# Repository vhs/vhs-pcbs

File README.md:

vhs-pcbs
========

PCB designs from vhs events

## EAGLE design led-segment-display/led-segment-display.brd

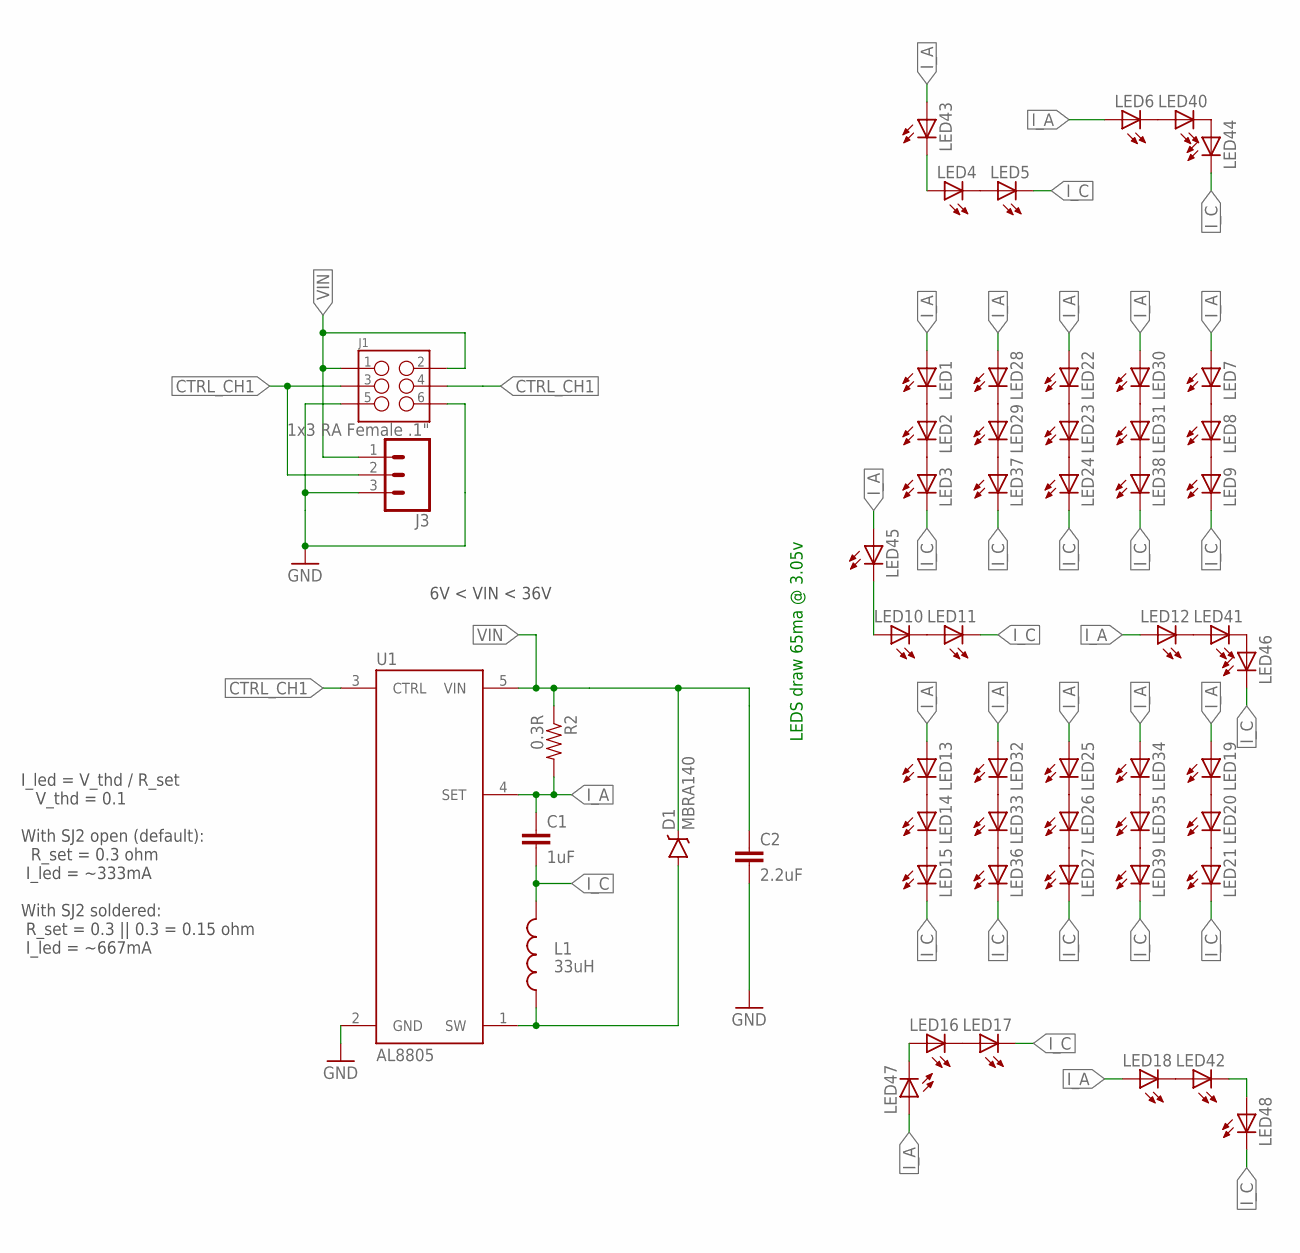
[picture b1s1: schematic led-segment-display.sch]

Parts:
C1: 1uF; 1206-CAP
C2: 2.2uF; 1206-CAP
D1: MBRA140; SMA-DIODE
J1: M03X2SMD; 2X3_SMD_2.54MM
J3: 1x3 RA Female .1"; 1X3_SMD_2.54MM
L1: 33uH; SRN6045
LED1, LED2, LED3, LED4, LED5, LED6, LED7, LED8, LED9, LED10, LED11, LED12, LED13, LED14, LED15, LED16, LED17, LED18, LED19, LED20, LED21, LED22, LED23, LED24, LED25, LED26, LED27, LED28, LED29, LED30, LED31, LED32, LED33, LED34, LED35, LED36, LED37, LED38, LED39, LED40, LED41, LED42, LED43, LED44, LED45, LED46, LED47, LED48: LED3014; LED-3014
R2: 0.3R; 0805
U1: AL8805; SOT23-5

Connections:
CTRL_CH1: J1.3, J1.4, J3.2, U1.3 (CTRL)
GND: C2.2, J1.5, J1.6, J3.3, U1.2 (GND)
I_A: C1.1, LED1.A, LED6.A, LED7.A, LED12.A, LED13.A, LED18.A, LED19.A, LED22.A, LED25.A, LED28.A, LED30.A, LED32.A, LED34.A, LED43.A, LED45.A, LED47.A, R2.2, U1.4 (SET)
I_C: C1.2, L1.2, LED3.C, LED5.C, LED9.C, LED11.C, LED15.C, LED17.C, LED21.C, LED24.C, LED27.C, LED36.C, LED37.C, LED38.C, LED39.C, LED44.C, LED46.C, LED48.C
unnamed: LED1.C, LED2.A
unnamed: LED2.C, LED3.A
unnamed: LED4.C, LED5.A
unnamed: LED4.A, LED43.C
unnamed: LED7.C, LED8.A
unnamed: LED8.C, LED9.A
unnamed: LED10.C, LED11.A
unnamed: LED40.C, LED44.A
unnamed: LED13.C, LED14.A
unnamed: LED14.C, LED15.A
unnamed: LED16.C, LED17.A
unnamed: LED42.C, LED48.A
unnamed: LED19.C, LED20.A
unnamed: LED20.C, LED21.A
unnamed: LED22.C, LED23.A
unnamed: LED23.C, LED24.A
unnamed: LED25.C, LED26.A
unnamed: LED26.C, LED27.A
unnamed: LED28.C, LED29.A
unnamed: LED30.C, LED31.A
unnamed: LED32.C, LED33.A
unnamed: LED34.C, LED35.A
unnamed: LED33.C, LED36.A
unnamed: LED29.C, LED37.A
unnamed: LED31.C, LED38.A
unnamed: LED35.C, LED39.A
unnamed: LED6.C, LED40.A
unnamed: LED12.C, LED41.A
unnamed: LED18.C, LED42.A
unnamed: LED16.A, LED47.C
unnamed: LED10.A, LED45.C
unnamed: LED41.C, LED46.A
SW: D1.A, L1.1, U1.1 (SW)
VIN: C2.1, D1.C, J1.1, J1.2, J3.1, R2.1, U1.5 (VIN)

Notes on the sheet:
LEDS draw 65ma @ 3.05v
I_led = V_thd / R_set V_thd = 0.1 With SJ2 open (default): R_set = 0.3 ohm I_led = ~333mA With SJ2 soldered: R_set = 0.3 || 0.3 = 0.15 ohm I_led = ~667mA
6V < VIN < 36V

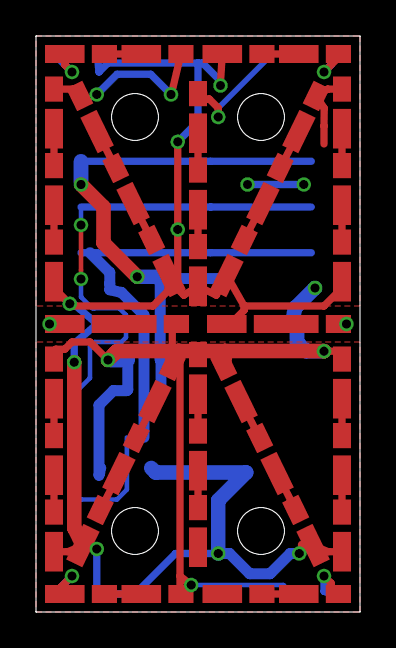
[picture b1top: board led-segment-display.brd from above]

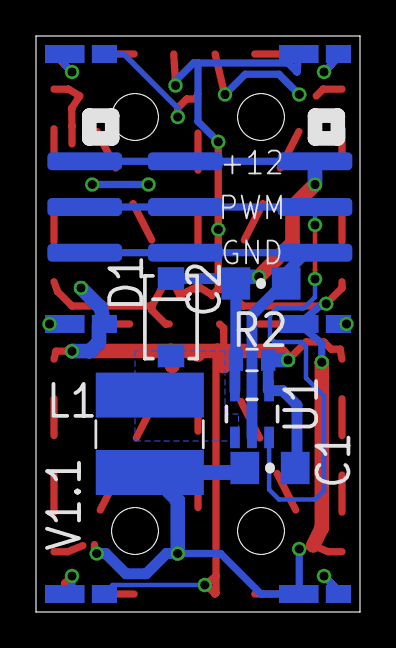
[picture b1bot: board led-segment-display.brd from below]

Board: 2 copper layers, 18.0 x 32.0 mm, 56 parts (14 on the bottom side), 38 nets.

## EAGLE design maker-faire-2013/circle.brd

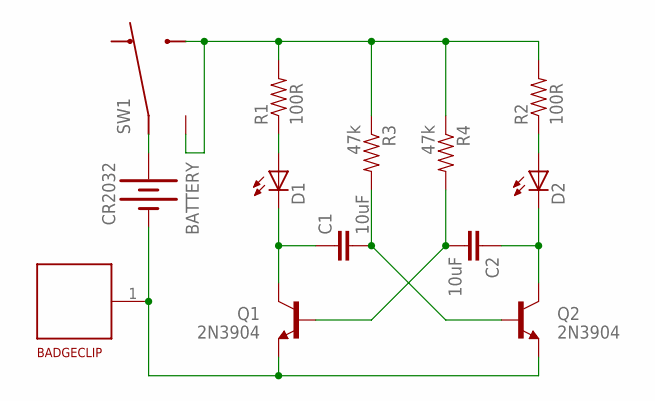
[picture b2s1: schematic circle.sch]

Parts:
BADGECLIP: BADGE_CLIP
BATTERY: CR2032; BATTCOM_20MM_PTH
C1, C2: 10uF; C050-024X044
D1, D2: LED5MM-KIT
Q1, Q2: 2N3904; TO-92-AMMO
R1, R2: 100R; AXIAL-0.4
R3, R4: 47k; AXIAL-0.4
SW1: 0S102011MS2QN1

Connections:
1: SW1.1
CASE2: R1.P$2 (2), R2.P$2 (2), R3.P$1 (1), R4.P$1 (1), SW1.3, SW1.CASE1 (CASE2), SW1.CASE2
GND: BADGECLIP.1, BATTERY.2 (-), Q1.1 (E), Q2.1 (E)
unnamed: BATTERY.1 (+), SW1.2
unnamed: C2.1, D2.K (C), Q2.3 (C)
unnamed: C1.1, D1.K (C), Q1.3 (C)
unnamed: C2.2, Q1.2 (B), R4.P$2 (2)
unnamed: C1.2, Q2.2 (B), R3.P$2 (2)
unnamed: D2.A, R2.P$1 (1)
unnamed: D1.A, R1.P$1 (1)

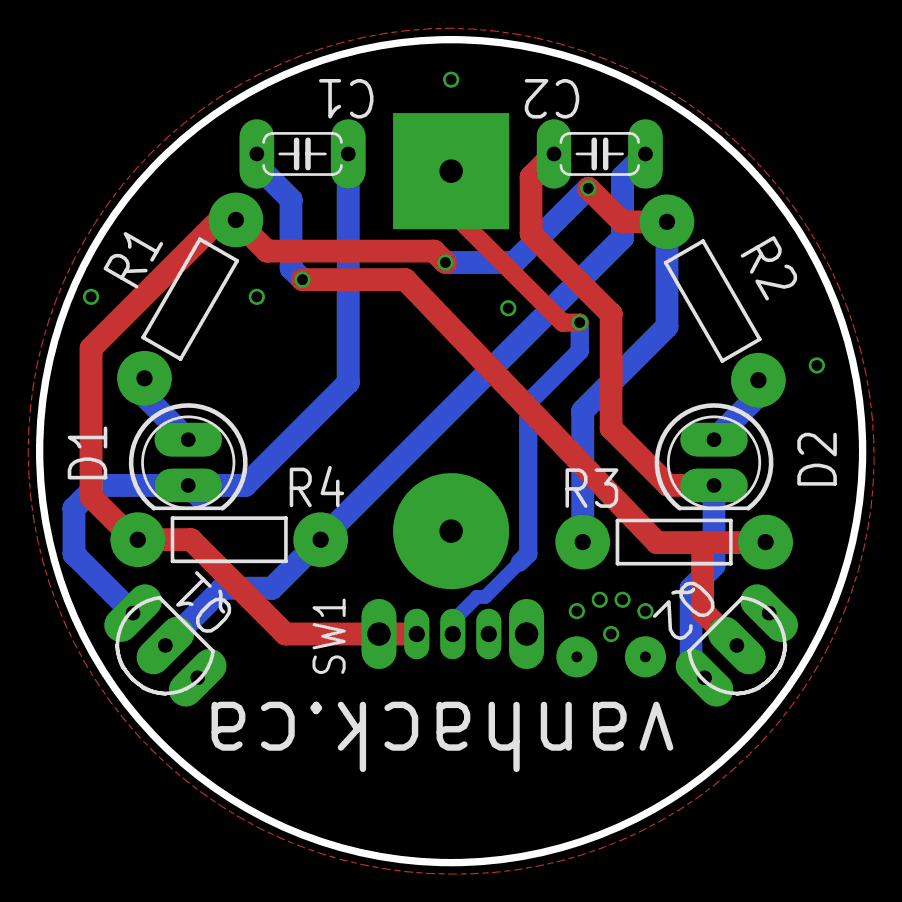
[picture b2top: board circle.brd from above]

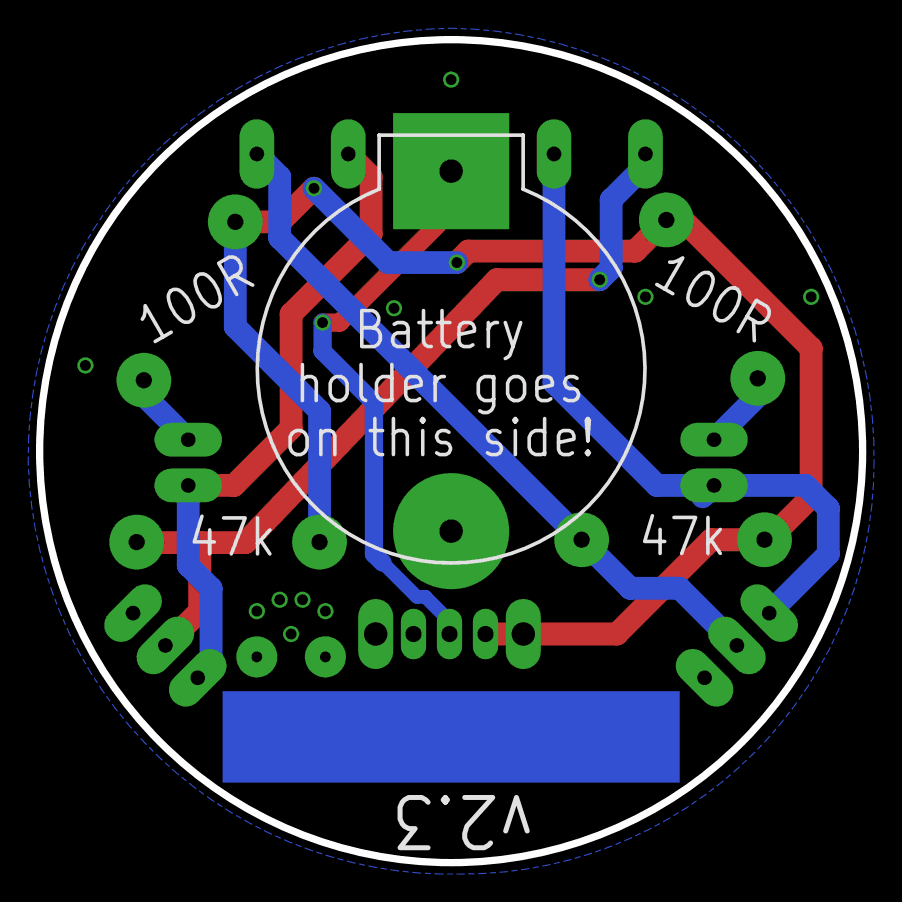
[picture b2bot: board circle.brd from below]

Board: 2 copper layers, 45.7 x 45.7 mm, 14 parts (2 on the bottom side), 9 nets.

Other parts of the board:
U$1: VHS-LOGO-SMALL

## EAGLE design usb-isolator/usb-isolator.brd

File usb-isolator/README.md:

USB Isolator PCB
================

Notes
-----

This is a very simple PCB so little documentation is needed.  Information
about the isolation can be found in the ADUM3160 [data sheet](http://www.analog.com/en/interface-isolation/digital-isolators/adum3160/products/product.html).

It is VERY important to realise that the power needs to come from a plug
pack and not the computer.  Supplying power to the power input from the
computer removes most of the isolation (data is still isolated).

Note that pin one is not marked on early versions of the PCB. Please refer
to the photo in this repository.

Parts
-----

PCBs are for sale on [Tindie](https://www.tindie.com/products/TomKeddie/usb-isolator-pcb-only/)

All the USB connectors were originally purchased on ebay.

You may be able to get a sample of the ADUM3160BRWZ from Analog Devices.

The parts list is below, thanks to Mike for supplying the connector part numbers, the rest should be fairly easy to determine.

| Qty | Value | Device | Parts | Description | Digikey | 
| --- | ----- | ------ | ----- | ----------- | ------- |
| 2 | 10uF | C-EUC0805K | C1, C6 | 10uF 0805 Ceramic Capacitor | |
| 4 | 0.1uF | C-EUC0805K | C2, C3, C4, C5 | 0.1uF 0805 Ceramic Capacitor | |
| 1 | 47uF | CPOL-EUD/7343-31W | C7 | 47uF 2917 Size "D" Tantalum Capacitor | |
| 4 | 24R | R-EU_M0805 | R1, R2, R3, R4 | 24R 0805 5% resistor | |
| 1 | 10K | R-EU_M0805 | R5 | 10k 0805 5% resistor | |
| 2 | 1K | R-EU_M0805 | R6, R7 | 1k 0805 5% resistor (rev 1.2 and later) | |
| 2 | GREEN | LED-0805 | LED1, LED2 | Green 0805 LED (rev 1.2 and later) | |
| 1 | ADUM3160BRWZ | SO16W | IC1 | Analog Devices ADUM3160BRWZ | |
| 1 | CON-USB-F-2PB | CON-USB-F-2PB | USBOUT | USB SMD Female connector with 2 body pins | 1175-1016-ND |
| 2 | CON-USB-F-MINI-B | CONN_USB_MINI-B | POWER, USBIN | USB Mini Female connector | 609-4700-1-ND |
| 1 | PCB_DP_SQUARE-5X5 | DP5050_V1 | USB-ISOLATOR | USB Isolator PCB | NA |

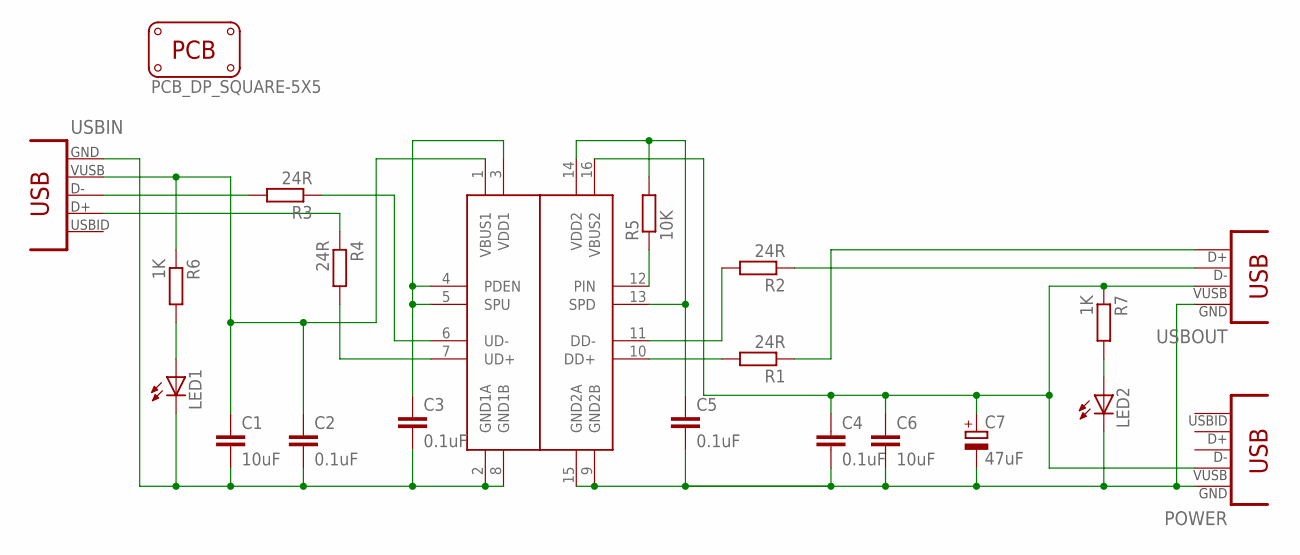
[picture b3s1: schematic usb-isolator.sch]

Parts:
C1, C6: 10uF; C0805K
C2, C3, C4, C5: 0.1uF; C0805K
C7: 47uF; D/7343-31W
IC1: ADUM3160BRWZ; SO16W
LED1, LED2: LED-0805; LED-805
POWER: CON-USB-F-MINI-B; CONN_USB_MINI-B
R1, R2, R3, R4: 24R; M0805
R5: 10K; M0805
R6, R7: 1K; M0805
USB-ISOLATOR: PCB_DP_SQUARE-5X5; DP5050_V1
USBIN: CON-USB-F-MINI-B; CONN_USB_MINI-B
USBOUT: CON-USB-F-2PB; CONN_USB_A_F

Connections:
GND1: C1.2, C2.2, C3.2, IC1.2 (GND1A), IC1.8 (GND1B), LED1.C, USBIN.GND
GND2: C4.2, C5.2, C6.2, C7.-, IC1.9 (GND2B), IC1.15 (GND2A), LED2.C, POWER.GND, USBOUT.4 (GND)
unnamed: R3.2, USBIN.D-
unnamed: IC1.6 (UD-), R3.1
unnamed: R1.1, USBOUT.3 (D+)
unnamed: IC1.11 (DD-), R2.2
unnamed: IC1.10 (DD+), R1.2
unnamed: IC1.12 (PIN), R5.1
unnamed: R4.1, USBIN.D+
unnamed: R2.1, USBOUT.2 (D-)
unnamed: IC1.7 (UD+), R4.2
unnamed: C5.1, IC1.13 (SPD), IC1.14 (VDD2), R5.2
unnamed: C3.1, IC1.3 (VDD1), IC1.4 (PDEN), IC1.5 (SPU)
unnamed: LED1.A, R6.2
unnamed: LED2.A, R7.2
VBUS1: C1.1, C2.1, IC1.1 (VBUS1), R6.1, USBIN.VUSB
VBUS2: C4.1, C6.1, C7.+, IC1.16 (VBUS2), POWER.VUSB, R7.1, USBOUT.1 (VUSB)

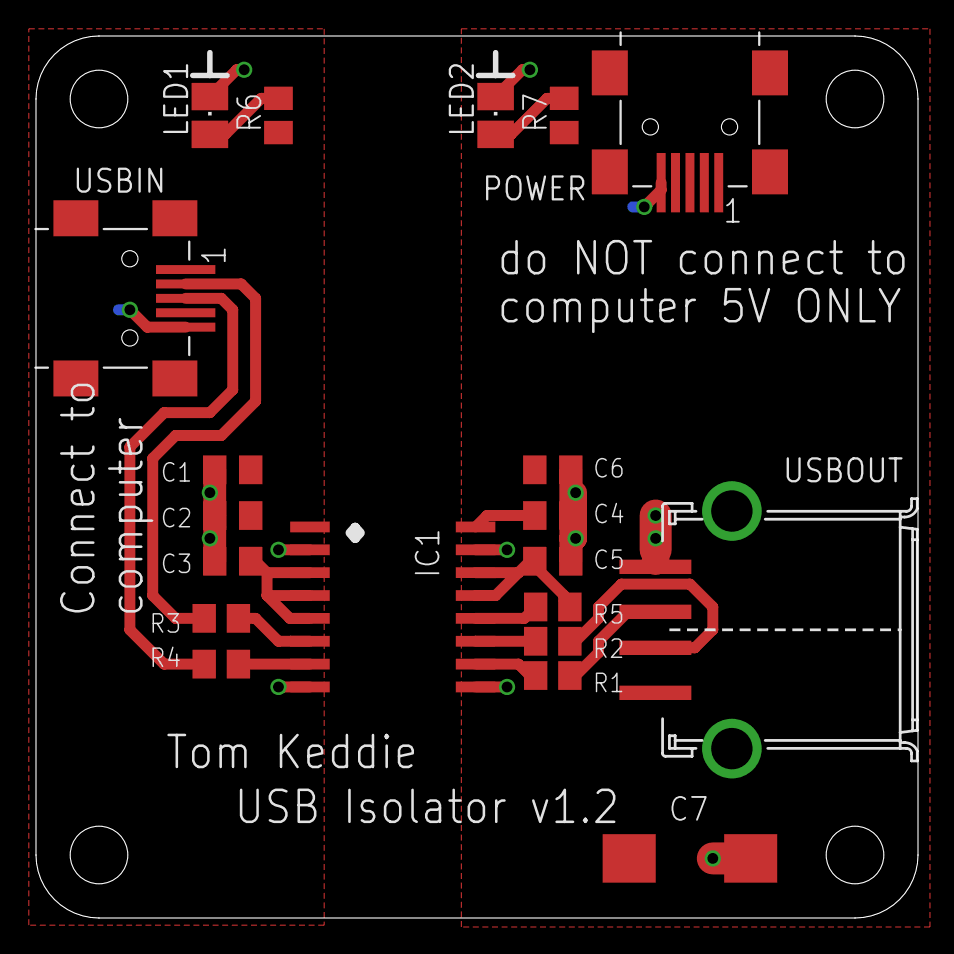
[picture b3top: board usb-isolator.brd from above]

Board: 2 copper layers, 49.0 x 49.0 mm, 22 parts (0 on the bottom side), 17 nets.

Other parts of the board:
U$1: VHS-LOGO-SMALL

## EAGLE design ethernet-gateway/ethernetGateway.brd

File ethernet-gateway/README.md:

## Internet of things board (aka Ethernet Gateway)

- derived from http://kehribar.me/hardware/ethernetGateway/

### Board mods (rev 0.3 PCB)

- cut power trace on underside, wire to header if desired
- cut trace to CTS and rewire to RTS

### Bootloader

Build optiboot for 8MHz and 57600 baud  (source at https://code.google.com/p/optiboot/)
```
make MCU_TARGET=atmega328p AVR_FREQ=8000000L TIMEOUT_MS=12000 BAUD_RATE=57600
```

### Program with bus pirate
```
avrdude -c stk500v2 -p m328p -P /dev/tty.usbserial-A501BZQP -v -U flash:w:optiboot_atmega328.hex 
```

### Set fuses
```
avrdude -c stk500v2 -p m328p -P /dev/tty.usbserial-A501BZQP -v -U lfuse:w:0xe2:m -U hfuse:w:0xde:m -U efuse:w:0x05:m

avrdude: safemode: lfuse reads as E2
avrdude: safemode: hfuse reads as DE
avrdude: safemode: efuse reads as 5
```

### Invert CTS using windows ft_prog utility

### Setup Arduino environment
Add entry to boards.txt for 8MHz/57600 baud

```
##############################################################
uno8.name=Arduino Uno (Internal Oscillator)
uno8.upload.protocol=arduino
uno8.upload.maximum_size=32256
uno8.upload.speed=57600
uno8.bootloader.low_fuses=0xe2
uno8.bootloader.high_fuses=0xde
uno8.bootloader.extended_fuses=0x05
uno8.bootloader.path=optiboot_8MHz
uno8.bootloader.file=optiboot_8MHz_atmega328.hex
uno8.bootloader.unlock_bits=0x3F
uno8.bootloader.lock_bits=0x0F
uno8.build.mcu=atmega328p
uno8.build.f_cpu=8000000L
uno8.build.core=arduino
uno8.build.variant=standard

##############################################################
```

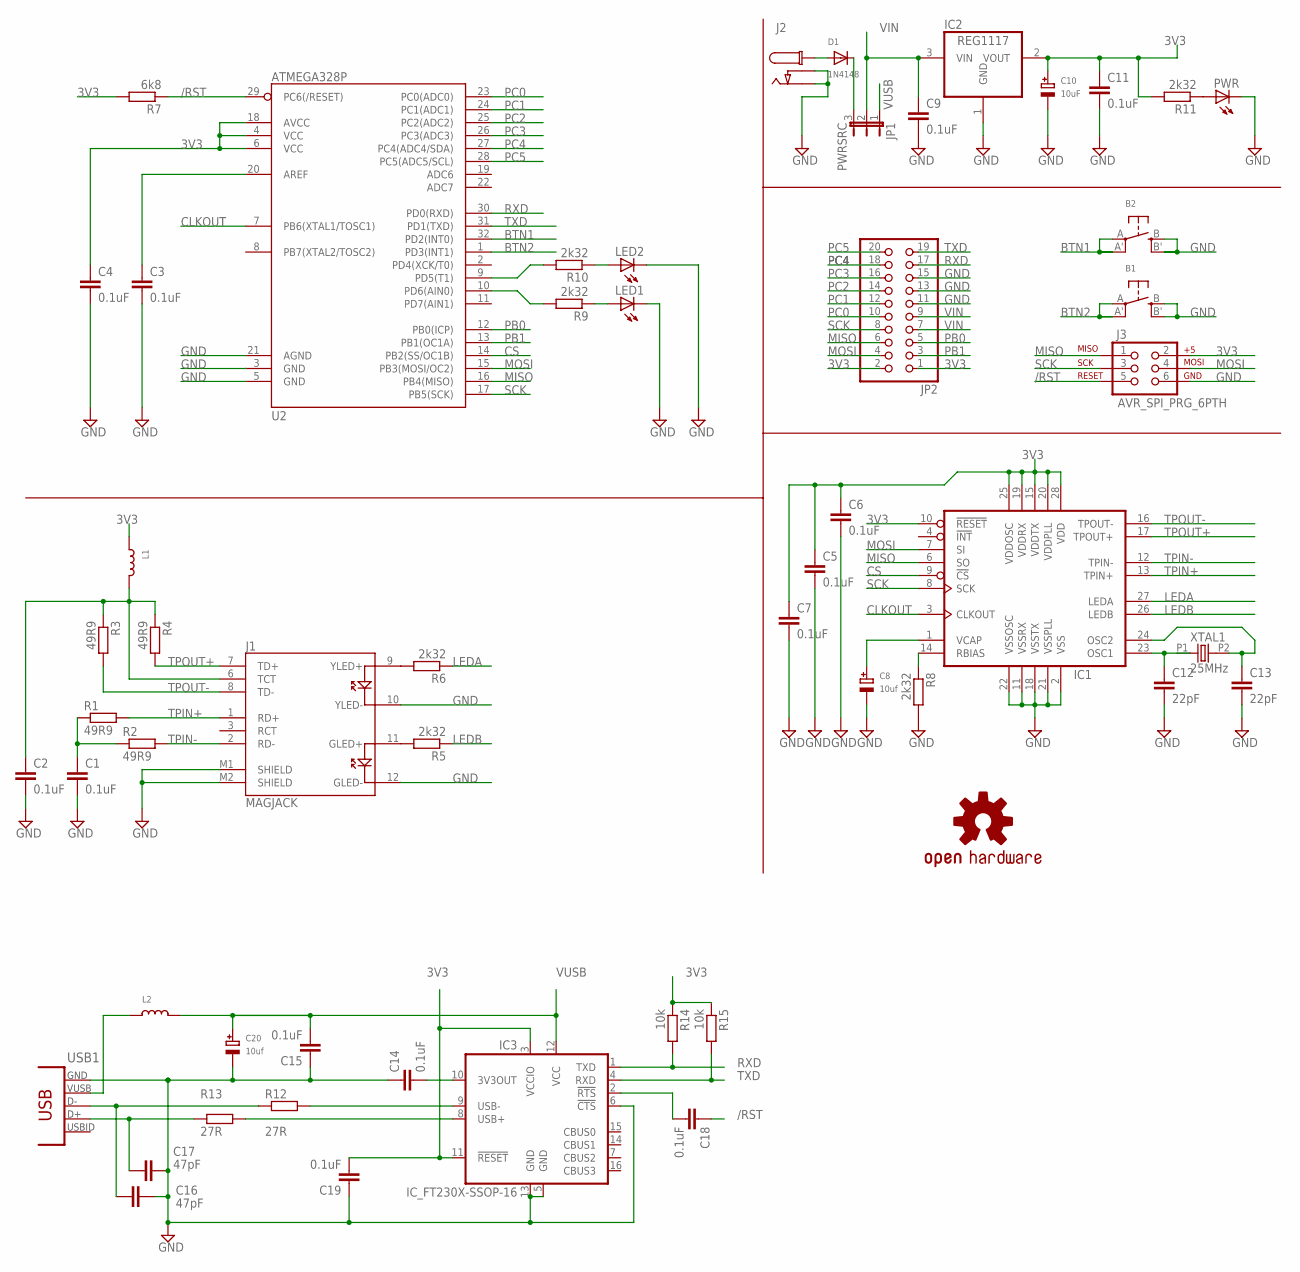
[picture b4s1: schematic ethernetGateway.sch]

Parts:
B1, B2: SWITCH_TACT_SMT4.6X2.8; BTN_KMR2_4.6X2.8
C1, C2, C3, C4, C5, C6, C7, C9, C11, C14, C15, C18, C19: 0.1uF; C0805
C8, C20: 10uf; EIA7343-31/D-R
C10: 10uF; EIA7343-31/D-R
C12, C13: 22pF; C0805
C16, C17: 47pF; C0805
D1: 1N4148; SMADIODE
IC1: IC_ENC28J60-SOIC-28; SOIC-28W
IC2: REG1117; SOT223
IC3: IC_FT230X-SSOP-16; SSOP-16-FTDI
J1: MAGJACK
J2: CON_DC_M-DC_PTH; DC_BARREL_JACK_PTH_2MM
J3: AVR_SPI_PRG_6PTH; 2X3
JP1: PWRSRC; JP2W
JP2: PINHD-2X10; 2X10
L1, L2: INDUCTOR0805; 0805
LED1, LED2: LED-0805; LED-805
LOGO1: OSHW-LOGOL; OSHW-LOGO-L
PWR: LED-0805; LED-805
R1, R2, R3, R4: 49R9; R0805
R5, R6, R8, R9, R10, R11: 2k32; R0805
R7: 6k8; R0805
R12, R13: 27R; M0805
R14, R15: 10k; R0805
U2: ATMEGA328P; TQFP32-08
USB1: CON-USB-F-MINI-B; CONN_USB_MINI-B
XTAL1: 25MHz; HC-49U-PTH

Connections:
3V3: C4.1, C5.1, C6.1, C7.1, C10.+, C11.1, C19.2, IC1.10 (!RESET), IC1.15 (VDDTX), IC1.19 (VDDRX), IC1.20 (VDDPLL), IC1.25 (VDDOSC), IC1.28 (VDD), IC2.2 (VOUT), IC3.3 (VCCIO), IC3.11 (!RESET), J3.2, JP2.1, JP2.2, L1.1, R7.2, R11.2, R14.1, R15.1, U2.4 (VCC), U2.6 (VCC), U2.18 (AVCC)
/RST: C18.1, J3.5, R7.1, U2.29 (PC6(/RESET))
BTN1: B2.A, B2.A' (P1), U2.32 (PD2(INT0))
BTN2: B1.A, B1.A' (P1), U2.1 (PD3(INT1))
CLKOUT: IC1.3 (CLKOUT), U2.7 (PB6(XTAL1/TOSC1))
CS: IC1.9 (!CS), U2.14 (PB2(SS/OC1B))
GND: B1.B (S), B1.B' (S1), B2.B (S), B2.B' (S1), C1.2, C2.2, C3.2, C4.2, C5.2, C6.2, C7.2, C8.-, C9.2, C10.-, C11.2, C12.2, C13.2, C14.1, C15.1, C16.1, C17.2, C19.1, C20.-, IC1.2 (VSS), IC1.11 (VSSRX), IC1.18 (VSSTX), IC1.21 (VSSPLL), IC1.22 (VSSOSC), IC2.1 (GND), IC3.5 (GND), IC3.6 (!CTS), IC3.13 (GND), J1.10 (YLED-), J1.12 (GLED-), J1.M1 (SHIELD), J1.M2 (SHIELD), J2.P2 (P3), J2.P3 (P2), J3.6, JP2.11, JP2.13, JP2.15, LED1.C, LED2.C, PWR.C, R8.2, U2.3 (GND), U2.5 (GND), U2.21 (AGND), USB1.GND
LEDA: IC1.27 (LEDA), R6.1
LEDB: IC1.26 (LEDB), R5.1
MISO: IC1.6 (SO), J3.1, JP2.6, U2.16 (PB4(MISO))
MOSI: IC1.7 (SI), J3.4, JP2.4, U2.15 (PB3(MOSI/OC2))
unnamed: C1.1, R1.1, R2.1
unnamed: J1.9 (YLED+), R6.2
unnamed: C13.1, IC1.24 (OSC2), XTAL1.P2 (2)
unnamed: J1.11 (GLED+), R5.2
unnamed: C12.1, IC1.23 (OSC1), XTAL1.P1 (1)
unnamed: C16.2, R12.1, USB1.D-
unnamed: C2.1, J1.6 (TCT), L1.2, R3.1, R4.1
unnamed: C17.1, R13.1, USB1.D+
unnamed: IC3.9 (USB-), R12.2
unnamed: C8.+, IC1.1 (VCAP)
unnamed: IC3.8 (USB+), R13.2
unnamed: C3.1, U2.20 (AREF)
unnamed: IC1.14 (RBIAS), R8.1
unnamed: L2.1, USB1.VUSB
unnamed: C14.2, IC3.10 (3V3OUT)
unnamed: LED1.A, R9.1
unnamed: LED2.A, R10.1
unnamed: D1.C, JP1.3
unnamed: D1.A, J2.P1
unnamed: C18.2, IC3.2 (!RTS)
unnamed: R10.2, U2.9 (PD5(T1))
unnamed: R9.2, U2.10 (PD6(AIN0))
unnamed: PWR.A, R11.1
PB0: JP2.5, U2.12 (PB0(ICP))
PB1: JP2.3, U2.13 (PB1(OC1A))
PC0: JP2.10, U2.23 (PC0(ADC0))
PC1: JP2.12, U2.24 (PC1(ADC1))
PC2: JP2.14, U2.25 (PC2(ADC2))
PC3: JP2.16, U2.26 (PC3(ADC3))
PC4: JP2.18, U2.27 (PC4(ADC4/SDA))
PC5: JP2.20, U2.28 (PC5(ADC5/SCL))
RXD: IC3.1 (TXD), JP2.17, R14.2, U2.30 (PD0(RXD))
SCK: IC1.8 (SCK), J3.3, JP2.8, U2.17 (PB5(SCK))
TPIN+: IC1.13 (TPIN+), J1.1 (RD+), R1.2
TPIN-: IC1.12 (TPIN-), J1.2 (RD-), R2.2
TPOUT+: IC1.17 (TPOUT+), J1.7 (TD+), R4.2
TPOUT-: IC1.16 (TPOUT-), J1.8 (TD-), R3.2
TXD: IC3.4 (RXD), JP2.19, R15.2, U2.31 (PD1(TXD))
VIN: C9.1, IC2.3 (VIN), JP1.2, JP2.7, JP2.9
VUSB: C15.2, C20.+, IC3.12 (VCC), JP1.1, L2.2

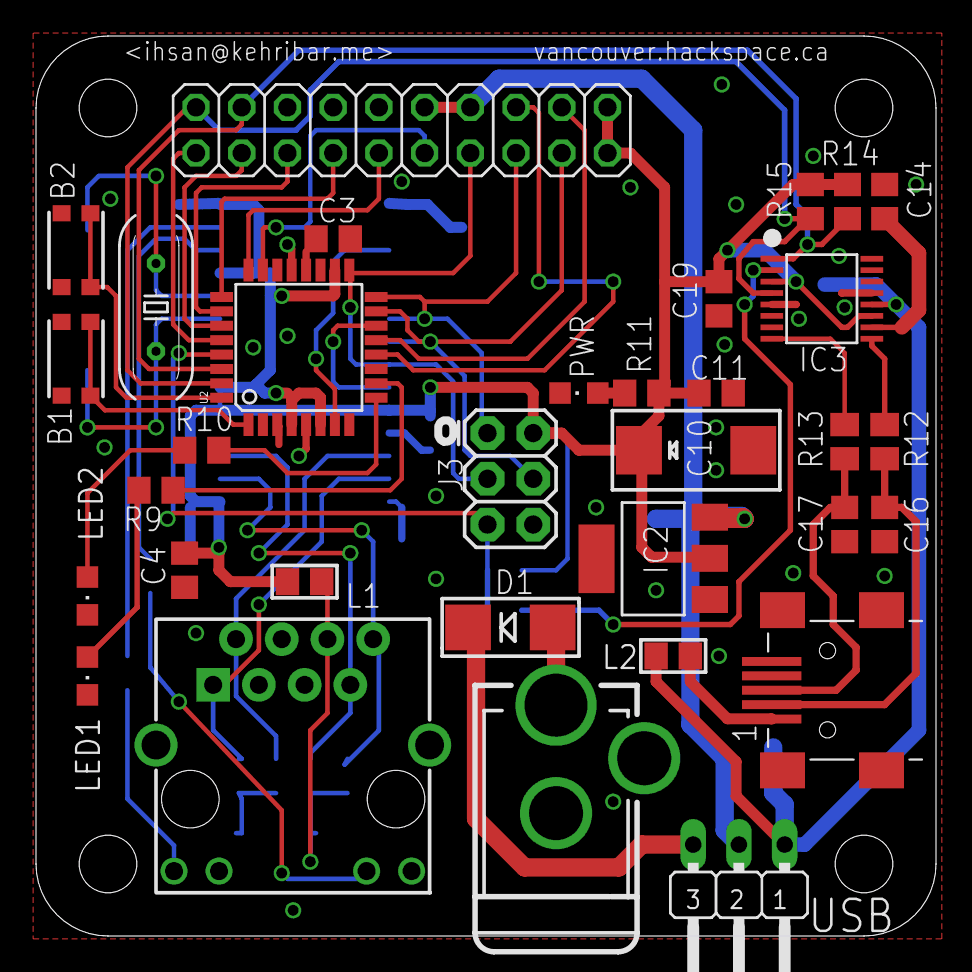
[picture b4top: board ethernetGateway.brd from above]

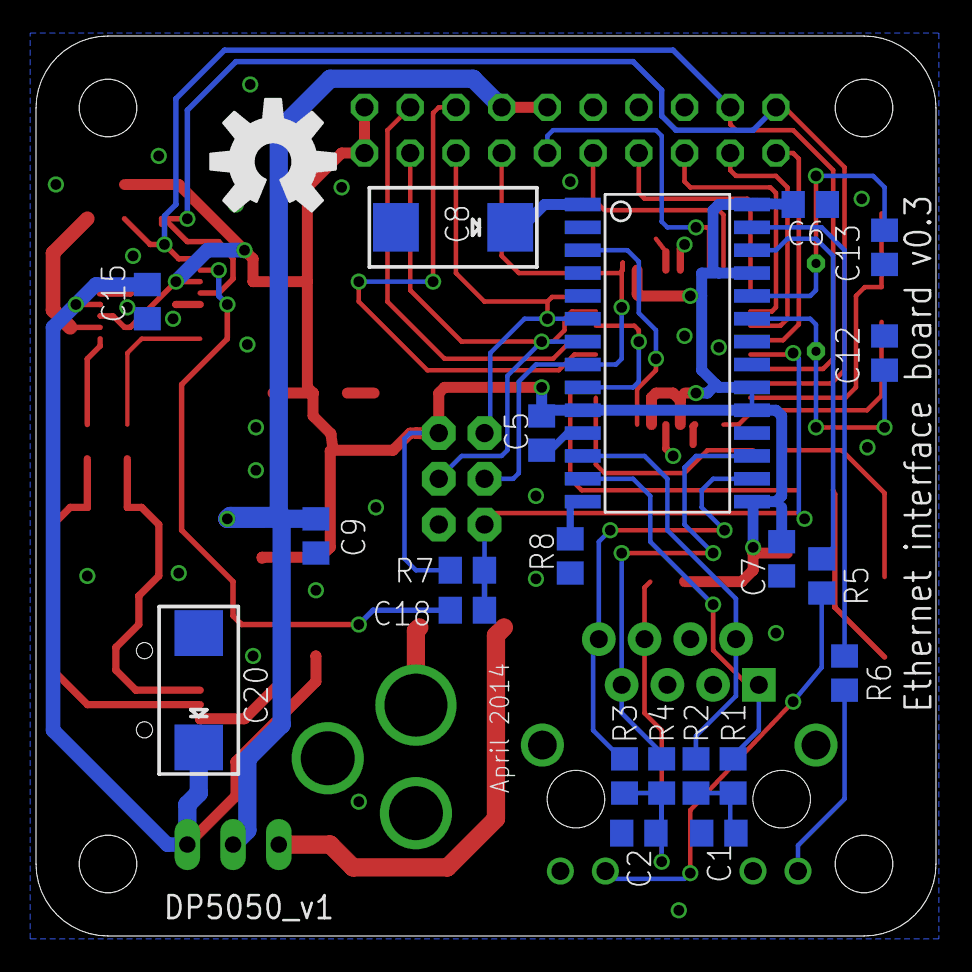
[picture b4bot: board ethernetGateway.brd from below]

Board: 2 copper layers, 50.0 x 50.0 mm, 56 parts (22 on the bottom side), 51 nets.

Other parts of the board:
U$1: DP5050_V1

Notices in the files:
parts and their libraries:
SparkFun-DigitalIC_ihsan: Licensing: CC v3.0 Share-Alike You are welcome to use this library for commercial purposes.
microbuilder: This work is placed in the public domain, and may be freely used for commercial and non-commercial work with the following conditions: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
